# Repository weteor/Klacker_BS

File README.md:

# Klacker_BS

a 3x5+2 split keyboard hidden in a row staggered unibody design w/ numpad

## Features

- MX hotswap
- compact design
- layout for comfortable typing, straight wrist and minimal fingermovement
- reversable pcb w/ numpad breakoff - Layout options: Numpad Right, Left or None
- Bluetooth and USB connection 
- case files are supplied (stl, step, as well as freecad files)
- ZMK firmware support

## Layout

Dots mark the home row. Colors indicate which finger is responsible for each key. It is essentially a 3x5+2 split and every keymap made for those will work on the Klacker. White keys except thumbs are free. I use the right ones as thumbkeys when I use the numpad.
It takes some time to adjust to the layout, but it is really comfortable to type on once the figers have adjusted.

## Want to build one?
You will find all production files needed to build your own [here](./prod).
I've included smt assembly files, but in the current times these might outdate quickly. If you can't figure out a replacement part, drop me a message and I will try to help out.

Case files can be found [here](./prod/case). The topside comes in two flavours. If you print at home with FDM printer, it might be better to use [prod/case/case_top_no_logo_FDM.stl](./prod/case/case_top_no_logo_FDM.stl). The top is completely flat and can be printed easily. If you use MJf or Resin use the other file

## cad data
Freecad source data for the case can be found [here](./cad_source). There are also step files if that's more helpful to you.
Plate can either be printed or made by your PCB manufacturer with the provided Kicad files.
Kicad data for plate and main pcb can be found [here](./pcb)

### firmware 
The Tipper TF uses ZMK firmware.

If you prefer the github workflow, you can find the zmk config for the Klacker BS [here](https://github.com/weteor/Klacker_BS-Config). 

## the rest
Everything in this repository is free to use however you might see fit. If you want to support me and my projects, please consider linking back to this repository if you build/change/use anything. 

If you would like to send me a tip, you could do it [here](https://ko-fi.com/weteor) (Please don't feel like you have to).

### pictures

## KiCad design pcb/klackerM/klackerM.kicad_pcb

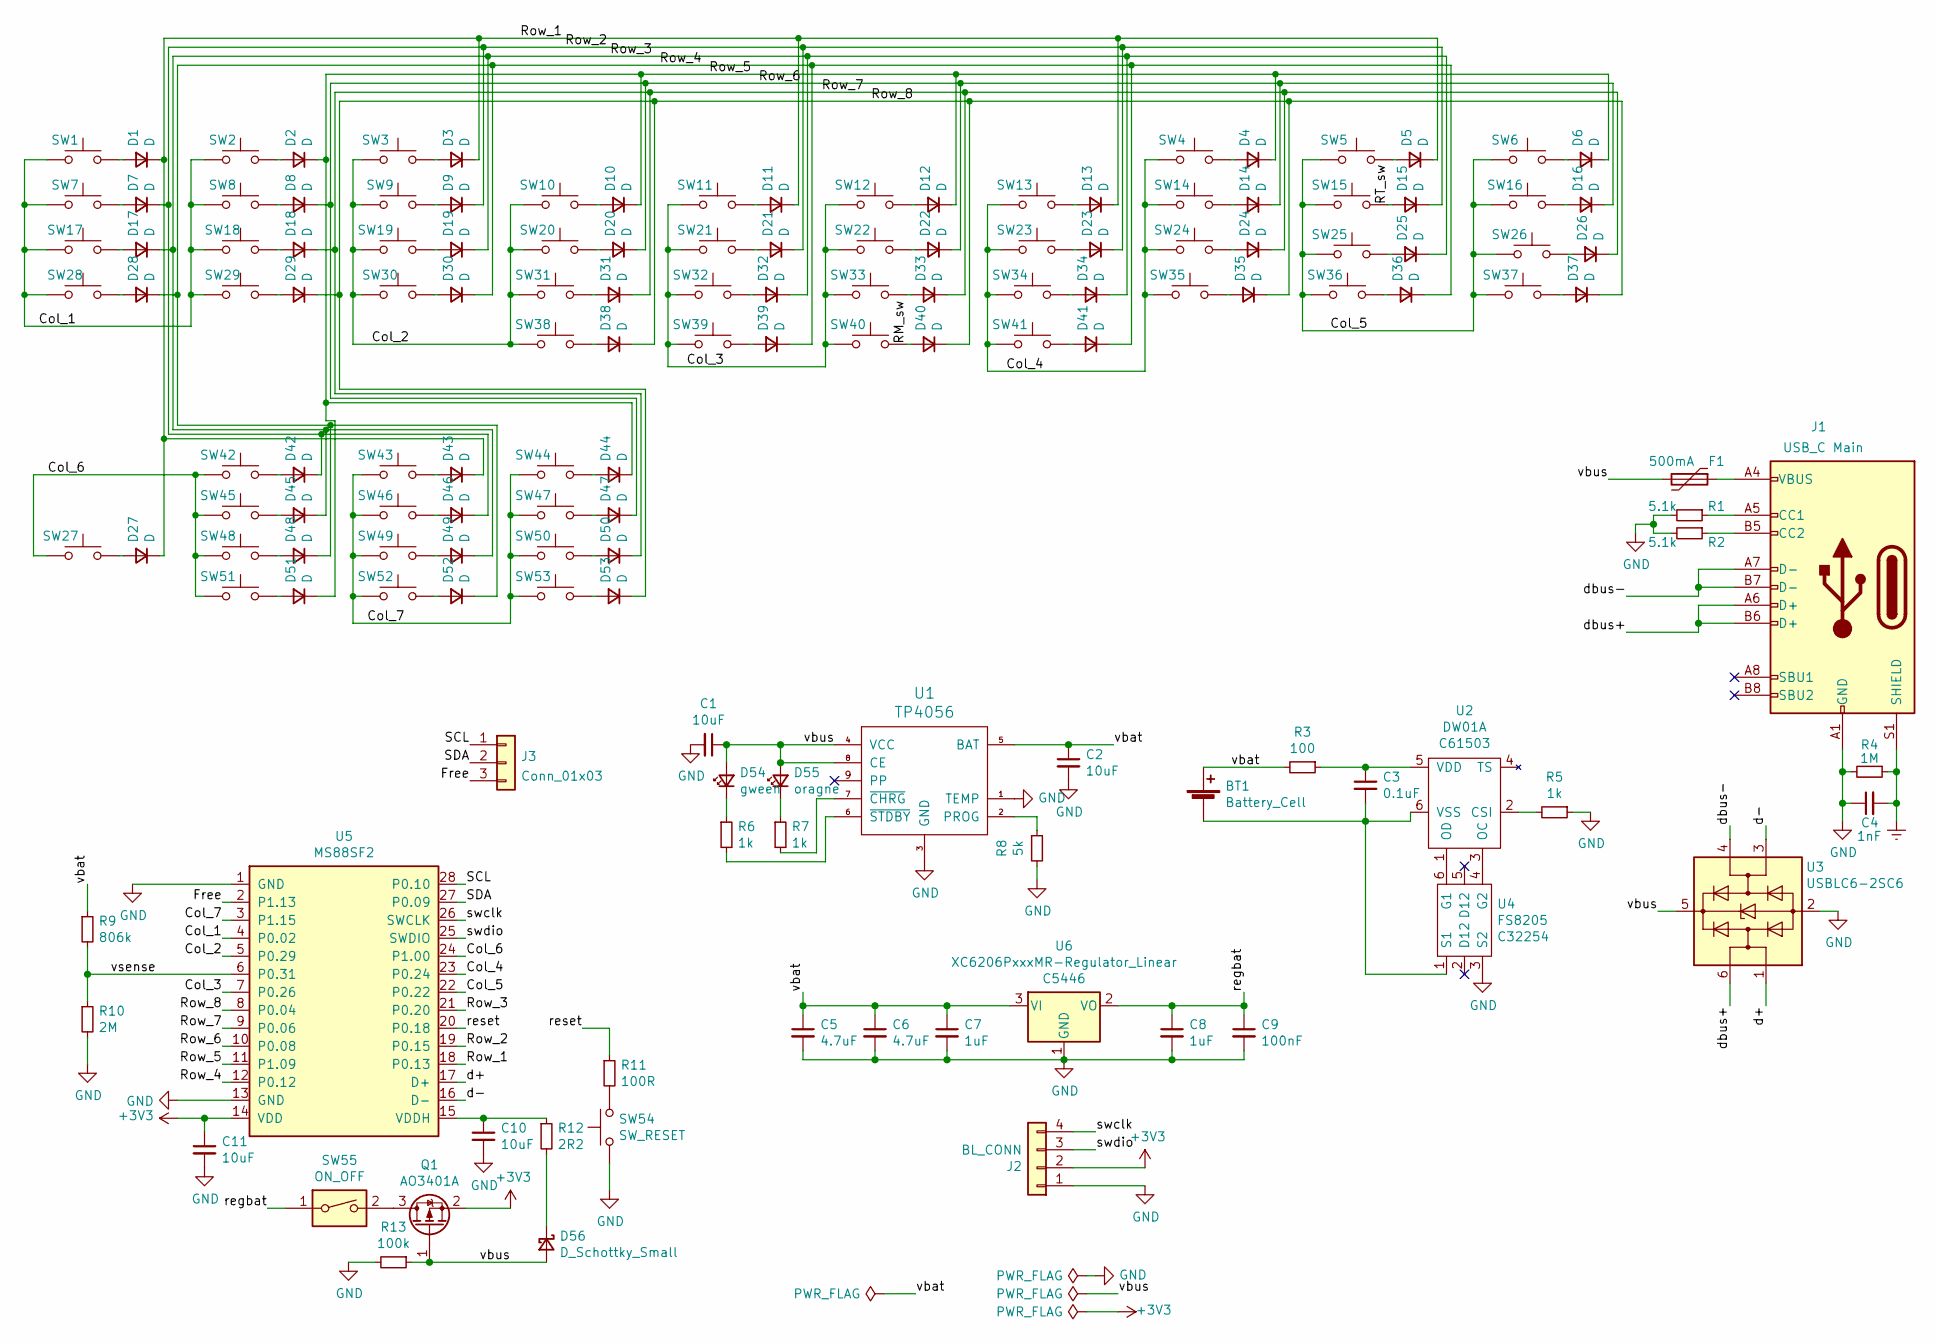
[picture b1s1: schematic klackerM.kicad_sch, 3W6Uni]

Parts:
BT1: Battery_Cell; Molex PicoBlade 2Pin smt tht
C1, C2, C10, C11: 10uF; C_0805_2012Metric
C3: 0.1uF; C_0805_2012Metric
C4: 1nF; C_0805_2012Metric
C5, C6: 4.7uF; C_0805_2012Metric
C7, C8: 1uF; C_0805_2012Metric
C9: 100nF; C_0805_2012Metric
D1, D2, D3, D4, D5, D6, D7, D8, D9, D10, D11, D12, D13, D14, D15, D16, D17, D18, D19, D20, D21, D22, D23, D24, D25, D26, D27, D28, D29, D30, D31, D32, D33, D34, D35, D36, D37, D38, D39, D40, D41, D42, D43, D44, D45, D46, D47, D48, D49, D50, D51, D52, D53: D; D_SOD-123
D54: gween; D_0805_2012Metric
D55: oragne; D_0805_2012Metric
D56: D_Schottky_Small; D_SOD-323_HandSoldering
F1: 500mA; Fuse_1206_3216Metric
J1: USB_C Main; USB-C-12-Pin-MidMount
J2: BL_CONN; PinHeader_1x04_P2.54mm_Vertical
J3: Conn_01x03; PinHeader_1x03_P2.54mm_Vertical
Q1: AO3401A; SOT-23
R1, R2: 5.1k; R_0805_2012Metric_Pad1.20x1.40mm_HandSolder
R3: 100; R_0805_2012Metric_Pad1.20x1.40mm_HandSolder
R4: 1M; R_0805_2012Metric_Pad1.20x1.40mm_HandSolder
R5, R6, R7: 1k; R_0805_2012Metric_Pad1.20x1.40mm_HandSolder
R8: 5k; R_0805_2012Metric_Pad1.20x1.40mm_HandSolder
R9: 806k; R_0805_2012Metric_Pad1.20x1.40mm_HandSolder
R10: 2M; R_0805_2012Metric_Pad1.20x1.40mm_HandSolder
R11: 100R; R_0805_2012Metric_Pad1.20x1.40mm_HandSolder
R12: 2R2; R_0805_2012Metric_Pad1.20x1.40mm_HandSolder
R13: 100k; R_0805_2012Metric_Pad1.20x1.40mm_HandSolder
SW1, SW6: SW_Push; CherryMX_Hotswap_1.75u
SW2, SW3, SW4, SW5, SW8, SW9, SW10, SW11, SW12, SW13, SW14, SW15, SW17, SW18, SW19, SW20, SW21, SW22, SW23, SW24, SW25, SW26, SW27, SW29, SW30, SW31, SW32, SW33, SW34, SW35, SW36, SW38, SW41, SW42, SW43, SW44, SW45, SW46, SW47, SW48, SW49, SW50, SW51, SW52, SW53: SW_Push; CherryMX_Hotswap
SW7, SW16, SW28, SW37, SW39, SW40: SW_Push; CherryMX_Hotswap_1.5u
SW54: SW_RESET; Micro_Push_Button_3x6x2.5mm
SW55: ON_OFF; K3-2380S-E1 On-on
U1: TP4056; TP4056_SOP-8-PP
U2: DW01A; SOT-23-6; LCSC C61503
U3: USBLC6-2SC6; SOT-23-6
U4: FS8205; SOT-23-6; LCSC C32254
U5: MS88SF2; MINEW_MS88SF2
U6: XC6206PxxxMR-Regulator_Linear; SOT-23; LCSC C5446

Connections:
+3V3: C11.1, J2.2, Q1.2 (S), U5.14 (VDD)
/Col_1: SW1.1, SW2.1, SW7.1, SW8.1, SW17.1, SW18.1, SW28.1, SW29.1, U5.4 (P0.02)
/Col_2: SW3.1, SW9.1, SW10.1, SW19.1, SW20.1, SW30.1, SW31.1, SW38.1, U5.5 (P0.29)
/Col_3: SW11.1, SW12.1, SW21.1, SW22.1, SW32.1, SW33.1, SW39.1, SW40.1, U5.7 (P0.26)
/Col_4: SW4.1, SW13.1, SW14.1, SW23.1, SW24.1, SW34.1, SW35.1, SW41.1, U5.23 (P0.24)
/Col_5: SW5.1, SW6.1, SW15.1, SW16.1, SW25.1, SW26.1, SW36.1, SW37.1, U5.22 (P0.22)
/Col_6: SW27.1, SW42.1, SW45.1, SW48.1, SW51.1, U5.24 (P1.00)
/Col_7: SW43.1, SW44.1, SW46.1, SW47.1, SW49.1, SW50.1, SW52.1, SW53.1, U5.3 (P1.15)
/Free: J3.3, U5.2 (P1.13)
/RM_sw: D40.2 (A), SW40.2
/RT_sw: D15.2 (A), SW15.2
/Row_1: D1.1 (K), D3.1 (K), D5.1 (K), D11.1 (K), D13.1 (K), D27.1 (K), D43.1 (K), U5.18 (P0.13)
/Row_2: D7.1 (K), D9.1 (K), D15.1 (K), D21.1 (K), D23.1 (K), D42.1 (K), D46.1 (K), U5.19 (P0.15)
/Row_3: D17.1 (K), D19.1 (K), D25.1 (K), D32.1 (K), D34.1 (K), D45.1 (K), D49.1 (K), U5.21 (P0.20)
/Row_4: D28.1 (K), D30.1 (K), D36.1 (K), D39.1 (K), D41.1 (K), D48.1 (K), D52.1 (K), U5.12 (P0.12)
/Row_5: D2.1 (K), D4.1 (K), D6.1 (K), D10.1 (K), D12.1 (K), D44.1 (K), D51.1 (K), U5.11 (P1.09)
/Row_6: D8.1 (K), D14.1 (K), D16.1 (K), D20.1 (K), D22.1 (K), D47.1 (K), U5.10 (P0.08)
/Row_7: D18.1 (K), D24.1 (K), D26.1 (K), D31.1 (K), D33.1 (K), D50.1 (K), U5.9 (P0.06)
/Row_8: D29.1 (K), D35.1 (K), D37.1 (K), D38.1 (K), D40.1 (K), D53.1 (K), U5.8 (P0.04)
/SCL: J3.1, U5.28 (P0.10)
/SDA: J3.2, U5.27 (P0.09)
/d+: U3.1 (I/O1), U5.17 (D+)
/d-: U3.3 (I/O2), U5.16 (D-)
/dbus+: J1.A6 (D+), J1.B6 (D+), U3.6 (I/O1)
/dbus-: J1.A7 (D-), J1.B7 (D-), U3.4 (I/O2)
/regbat: C8.1, C9.1, SW55.1, U6.2 (VO)
/reset: R11.1, U5.20 (P0.18)
/swclk: J2.4, U5.26 (SWCLK)
/swdio: J2.3, U5.25 (SWDIO)
/vbat: BT1.1 (+), C2.1, C5.1, C6.1, C7.1, R3.2, R9.1, U1.5 (BAT), U6.3 (VI)
/vbus: C1.1, D54.2 (A), D55.2 (A), D56.2 (A), F1.2, Q1.1 (G), R13.1, U1.4 (VCC), U1.8 (CE), U3.5 (VBUS)
/vsense: R9.2, R10.1, U5.6 (P0.31)
Earth: C4.2, J1.S1 (SHIELD), R4.1
GND: C1.2, C2.2, C4.1, C5.2, C6.2, C7.2, C8.2, C9.2, C10.2, C11.2, J1.A1 (GND), J1.A12 (GND), J1.B1 (GND), J1.B12 (GND), J2.1, R1.2, R2.2, R4.2, R5.1, R8.2, R10.2, R13.2, SW54.1, U1.1 (TEMP), U1.3 (GND), U3.2 (GND), U4.3 (S2), U5.1 (GND), U5.13 (GND), U6.1 (GND)
unnamed: BT1.2 (-), C3.2, U2.6 (VSS), U4.1 (S1)
unnamed: C3.1, R3.1, U2.5 (VDD)
unnamed: C10.1, R12.1, U5.15 (VDDH)
unnamed: D1.2 (A), SW1.2
unnamed: D2.2 (A), SW2.2
unnamed: D3.2 (A), SW3.2
unnamed: D4.2 (A), SW4.2
unnamed: D5.2 (A), SW5.2
unnamed: D6.2 (A), SW6.2
unnamed: D7.2 (A), SW7.2
unnamed: D8.2 (A), SW8.2
unnamed: D9.2 (A), SW9.2
unnamed: D10.2 (A), SW10.2
unnamed: D11.2 (A), SW11.2
unnamed: D12.2 (A), SW12.2
unnamed: D13.2 (A), SW13.2
unnamed: D14.2 (A), SW14.2
unnamed: D16.2 (A), SW16.2
unnamed: D17.2 (A), SW17.2
unnamed: D18.2 (A), SW18.2
unnamed: D19.2 (A), SW19.2
unnamed: D20.2 (A), SW20.2
unnamed: D21.2 (A), SW21.2
unnamed: D22.2 (A), SW22.2
unnamed: D23.2 (A), SW23.2
unnamed: D24.2 (A), SW24.2
unnamed: D25.2 (A), SW25.2
unnamed: D26.2 (A), SW26.2
unnamed: D27.2 (A), SW27.2
unnamed: D28.2 (A), SW28.2
unnamed: D29.2 (A), SW29.2
unnamed: D30.2 (A), SW30.2
unnamed: D31.2 (A), SW31.2
unnamed: D32.2 (A), SW32.2
unnamed: D33.2 (A), SW33.2
unnamed: D34.2 (A), SW34.2
unnamed: D35.2 (A), SW35.2
unnamed: D36.2 (A), SW36.2
unnamed: D37.2 (A), SW37.2
unnamed: D38.2 (A), SW38.2
unnamed: D39.2 (A), SW39.2
unnamed: D41.2 (A), SW41.2
unnamed: D42.2 (A), SW42.2
unnamed: D43.2 (A), SW43.2
unnamed: D44.2 (A), SW44.2
unnamed: D45.2 (A), SW45.2
unnamed: D46.2 (A), SW46.2
unnamed: D47.2 (A), SW47.2
unnamed: D48.2 (A), SW48.2
unnamed: D49.2 (A), SW49.2
unnamed: D50.2 (A), SW50.2
unnamed: D51.2 (A), SW51.2
unnamed: D52.2 (A), SW52.2
unnamed: D53.2 (A), SW53.2
unnamed: D54.1 (K), R6.1
unnamed: D55.1 (K), R7.1
unnamed: D56.1 (K), R12.2
unnamed: F1.1, J1.A4 (VBUS), J1.A9 (VBUS), J1.B4 (VBUS), J1.B9 (VBUS)
unnamed: J1.A5 (CC1), R1.1
unnamed: J1.B5 (CC2), R2.1
unnamed: Q1.3 (D), SW55.2
unnamed: R5.2, U2.2 (CSI)
unnamed: R6.2, U1.6 (~STDBY)
unnamed: R7.2, U1.7 (~CHRG)
unnamed: R8.1, U1.2 (PROG)
unnamed: R11.2, SW54.2
unnamed: U2.1 (OD), U4.6 (G1)
unnamed: U2.3 (OC), U4.4 (G2)

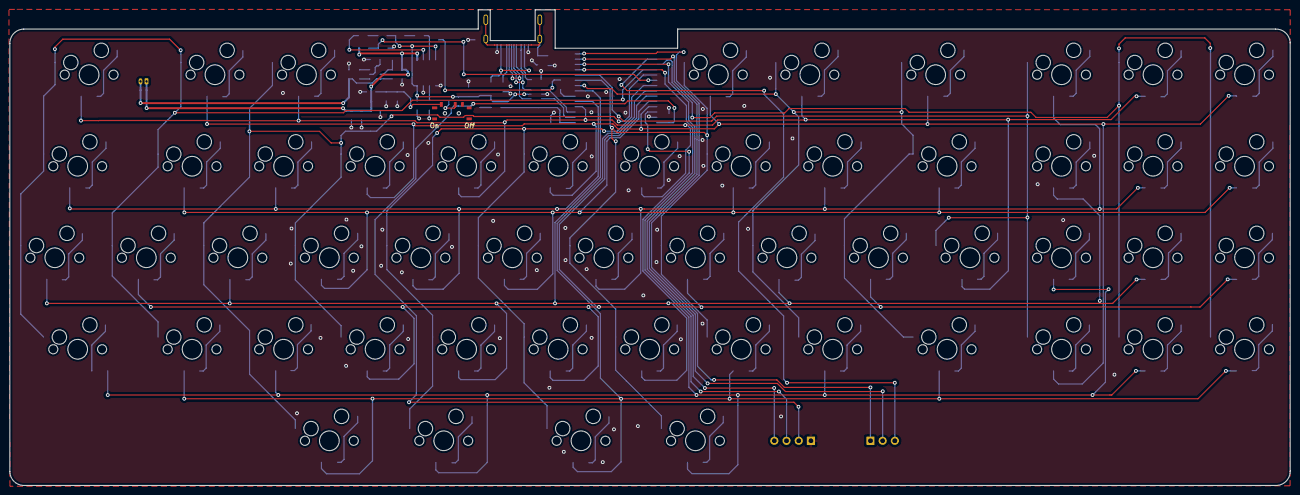
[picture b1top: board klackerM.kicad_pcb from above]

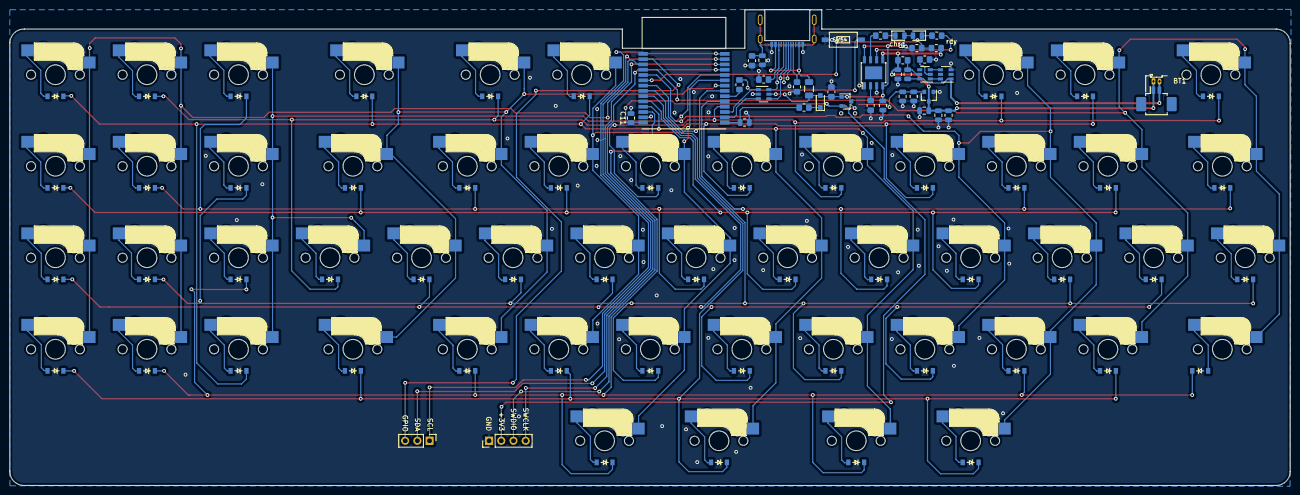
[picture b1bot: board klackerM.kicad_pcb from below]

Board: 2 copper layers, 266.5 x 99.0 mm, 147 parts (93 on the bottom side), 102 nets.

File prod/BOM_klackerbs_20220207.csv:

Comment,Designator,Footprint,LCSC
10uF,"C1,C2,C10,C11",Capacitor_SMD:C_0805_2012Metric,C15850
1nF,C4,Capacitor_SMD:C_0805_2012Metric,C46653
4.7uF,"C5,C6",Capacitor_SMD:C_0805_2012Metric,C1779
1uF,"C7,C8",Capacitor_SMD:C_0805_2012Metric,C28323
100nF,"C3,C9",Capacitor_SMD:C_0805_2012Metric,C49678
D,"D1,D2,D3,D4,D5,D6,D7,D8,D9,D10,D11,D12,D13,D14,D15,D16,D17,D18,D19,D20,D21,D22,D23,D24,D25,D26,D27,D28,D29,D30,D31,D32,D33,D34,D35,D36,D37,D38,D39,D40,D41,D42,D43,D44,D45,D46,D47,D48,D49,D50,D51,D52,D53",weteor:D_SOD-123,C81598
gween,D54,Diode_SMD:D_0805_2012Metric,C2297
oragne,D55,Diode_SMD:D_0805_2012Metric,C84256
D_Schottky_Small,D56,Diode_SMD:D_SOD-323_HandSoldering,C172430
500mA,F1,Fuse:Fuse_1206_3216Metric,C135336
USB_C Main,J1,weteor:USB-C-12-Pin-MidMount,C168688
AO3401A,Q1,Package_TO_SOT_SMD:SOT-23,C15127
5.1k,"R1,R2,R8",Resistor_SMD:R_0805_2012Metric_Pad1.20x1.40mm_HandSolder,C27834
2M,R10,Resistor_SMD:R_0805_2012Metric_Pad1.20x1.40mm_HandSolder,C26112
100R,"R3,R11",Resistor_SMD:R_0805_2012Metric_Pad1.20x1.40mm_HandSolder,C17408
2R2,R12,Resistor_SMD:R_0805_2012Metric_Pad1.20x1.40mm_HandSolder,C17521
100k,R13,Resistor_SMD:R_0805_2012Metric_Pad1.20x1.40mm_HandSolder,C149504
1M,R4,Resistor_SMD:R_0805_2012Metric_Pad1.20x1.40mm_HandSolder,C17514
1k,"R5,R6,R7",Resistor_SMD:R_0805_2012Metric_Pad1.20x1.40mm_HandSolder,C17513
806k,R9,Resistor_SMD:R_0805_2012Metric_Pad1.20x1.40mm_HandSolder,C63494
SW_RESET,SW54,weteor:Micro_Push_Button_3x6x2.5mm,C520860
TP4056,U1,weteor:TP4056_SOP-8-PP,C16581
DW01A,U2,Package_TO_SOT_SMD:SOT-23-6,C351410
USBLC6-2SC6,U3,Package_TO_SOT_SMD:SOT-23-6,C2827654
FS8205,U4,Package_TO_SOT_SMD:SOT-23-6,C2830320
XC6206PxxxMR-Regulator_Linear,U6,Package_TO_SOT_SMD:SOT-23,C5446

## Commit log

2022-01-21 add Licence file
2022-01-21 kicad files for main pcb and FR4 Plate
2022-01-21 freecad project for case
2022-01-21 production data, SMT Assembly and 3DP case
2022-01-21 add missing library for controlle module
2022-01-21 add step files for case
2022-01-21 add picture
2022-02-07 change: PCB reversable (numpad can be used left or right). Numpad can be cut off for smaller Version
2022-02-07 add new production files
2022-02-07 add cad sources for Left side numpad
2022-02-13 add new pictures
2022-02-13 new picture
2022-04-23 add vector plate files
2025-03-15 add case without numpad

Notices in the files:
pcb/klackerM/klackerM.kicad_sch:
Licensed under CERN-OHL-P v2
